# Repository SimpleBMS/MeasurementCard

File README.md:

This is a cool measurement card for SimpleBMS!

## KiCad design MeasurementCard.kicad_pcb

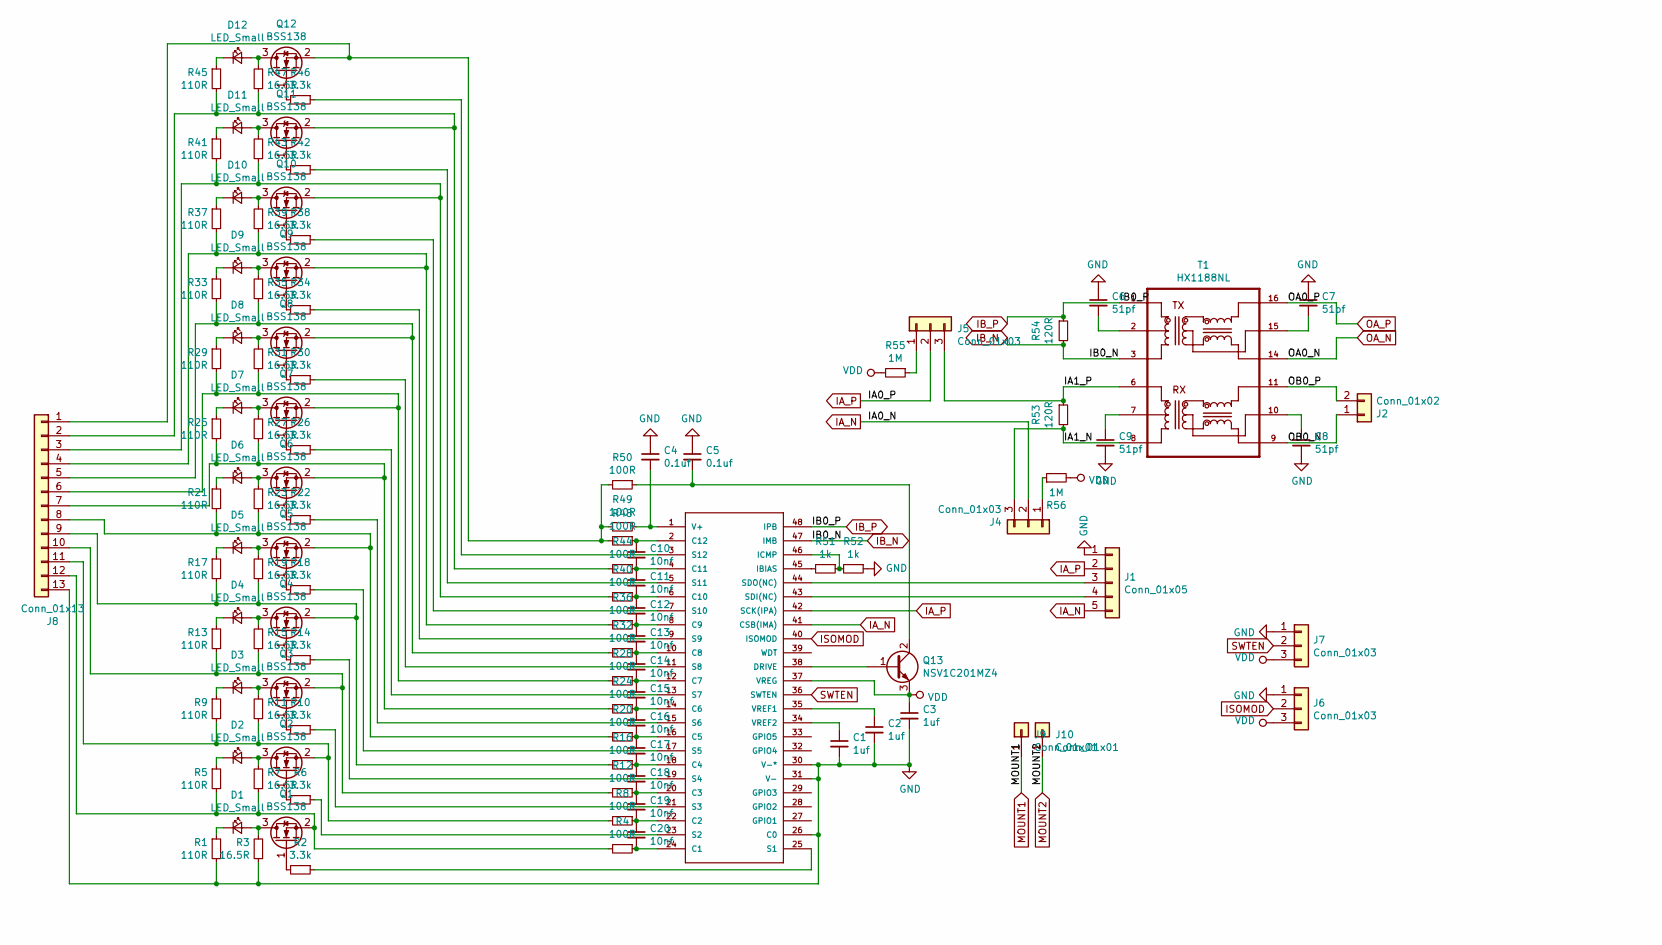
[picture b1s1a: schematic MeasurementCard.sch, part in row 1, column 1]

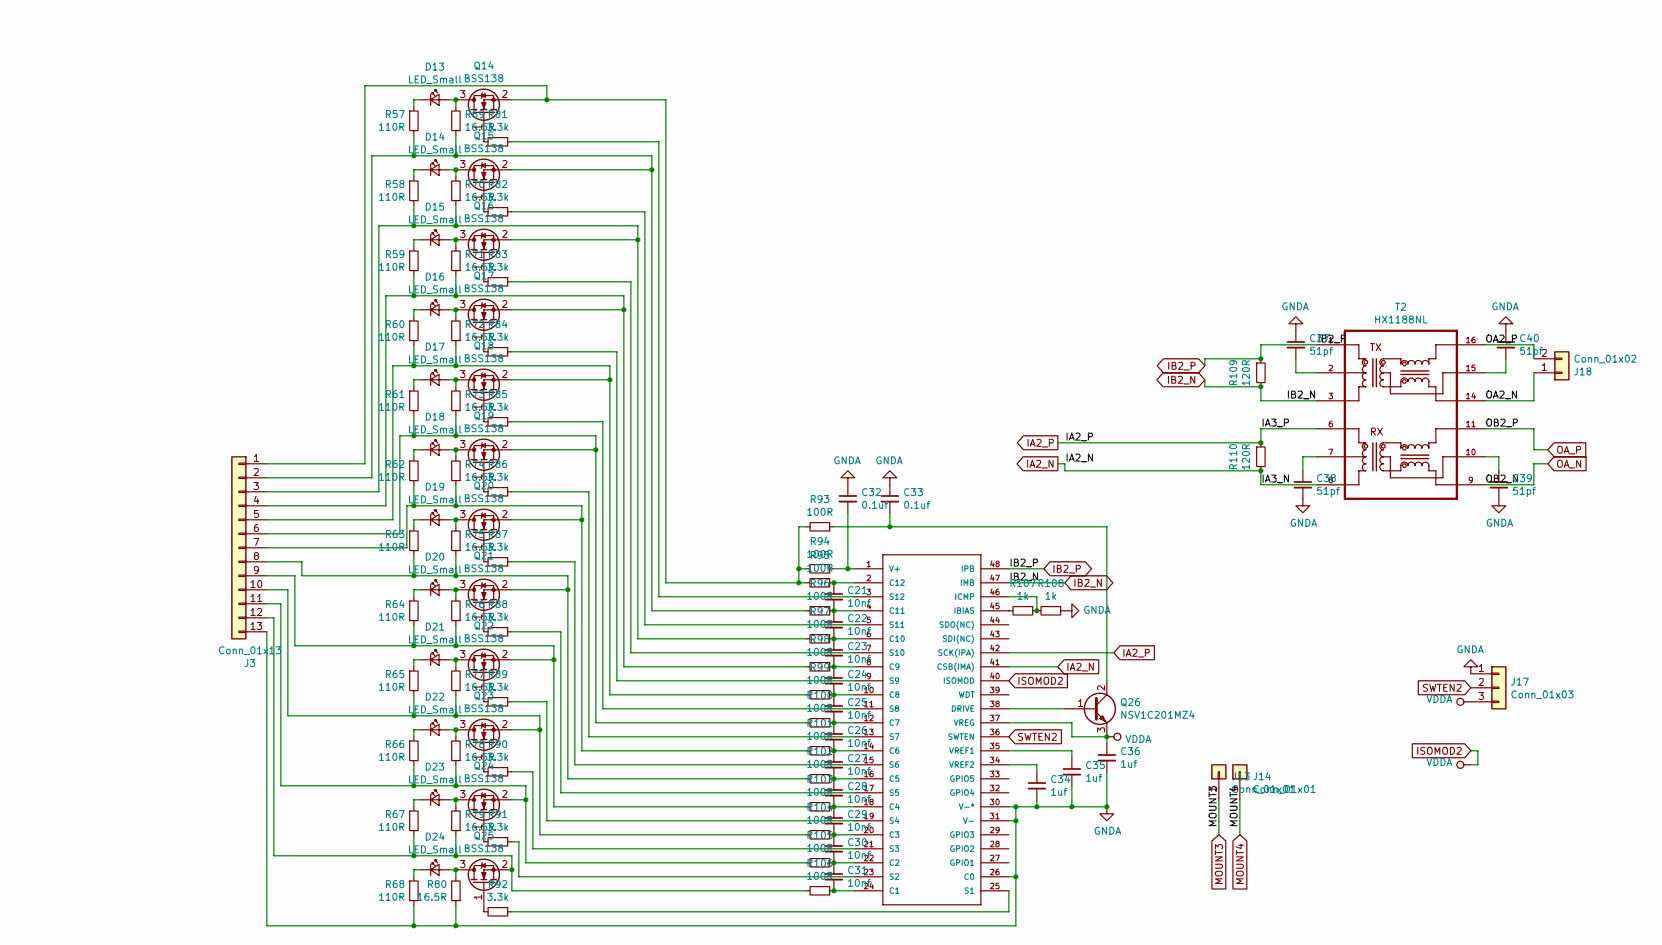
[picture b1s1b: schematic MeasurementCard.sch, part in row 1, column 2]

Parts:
C1, C2, C3, C34, C35, C36: 1uf; C_0805_2012Metric_Pad1.15x1.40mm_HandSolder
C4, C5, C32, C33: 0.1uf; C_0805_2012Metric_Pad1.15x1.40mm_HandSolder
C6, C7, C8, C9, C37, C38, C39, C40: 51pf; C_0805_2012Metric_Pad1.15x1.40mm_HandSolder
C10, C11, C12, C13, C14, C15, C16, C17, C18, C19, C20, C21, C22, C23, C24, C25, C26, C27, C28, C29, C30, C31: 10nf; C_0805_2012Metric_Pad1.15x1.40mm_HandSolder
D1, D2, D3, D4, D5, D6, D7, D8, D9, D10, D11, D12, D13, D14, D15, D16, D17, D18, D19, D20, D21, D22, D23, D24: LED_Small; LED_0603_1608Metric_Pad1.05x0.95mm_HandSolder
J1: Conn_01x05; JST_XH_S05B-XH-A_1x05_P2.50mm_Horizontal
J2, J18: Conn_01x02; JST_XH_S02B-XH-A_1x02_P2.50mm_Horizontal
J3, J8: Conn_01x13; JST_XH_S13B-XH-A_1x13_P2.50mm_Horizontal
J4, J5, J6, J7, J17: Conn_01x03; PinHeader_1x03_P2.54mm_Vertical
J9, J10, J13, J14: Conn_01x01; 1pin
Q1, Q2, Q3, Q4, Q5, Q6, Q7, Q8, Q9, Q10, Q11, Q12, Q14, Q15, Q16, Q17, Q18, Q19, Q20, Q21, Q22, Q23, Q24, Q25: BSS138; SOT-23
Q13, Q26: NSV1C201MZ4; SOT-223
R1, R5, R9, R13, R17, R21, R25, R29, R33, R37, R41, R45, R57, R58, R59, R60, R61, R62, R63, R64, R65, R66, R67, R68: 110R; R_0805_2012Metric_Pad1.15x1.40mm_HandSolder
R2, R6, R10, R14, R18, R22, R26, R30, R34, R38, R42, R46, R81, R82, R83, R84, R85, R86, R87, R88, R89, R90, R91, R92: 3.3k; R_0805_2012Metric_Pad1.15x1.40mm_HandSolder
R3, R7, R11, R15, R19, R23, R27, R31, R35, R39, R43, R47, R69, R70, R71, R72, R73, R74, R75, R76, R77, R78, R79, R80: 16.5R; R_2512_6332Metric_Pad1.52x3.35mm_HandSolder
R4, R8, R12, R16, R20, R24, R28, R32, R36, R40, R44, R48, R49, R50, R93, R94, R95, R96, R97, R98, R99, R100, R101, R102, R103, R104, R105, R106: 100R; R_0805_2012Metric_Pad1.15x1.40mm_HandSolder
R51, R52, R107, R108: 1k; R_0805_2012Metric_Pad1.15x1.40mm_HandSolder
R53, R54, R109, R110: 120R; R_0805_2012Metric_Pad1.15x1.40mm_HandSolder
R55, R56: 1M; R_0805_2012Metric_Pad1.15x1.40mm_HandSolder
T1, T2: HX1188NL; HXXXX
U1, U2: LTC6804-1; SOP50P780X200-48N

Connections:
/IA1_N: J4.3, R53.2, T1.8
/IA1_P: J5.3, R53.1, T1.6
/OA2_N: J18.1, T2.14
/OA2_P: J18.2, T2.16
/OB0_N: J2.1, T1.9
/OB0_P: J2.2, T1.11
GND: C1.2, C2.2, C3.2, C4.1, C5.1, C6.1, C7.1, C8.2, C9.2, J1.1, J6.1, J7.1, J8.13, R1.2, R3.1, R52.1, U1.26 (C0), U1.30 (V-*), U1.31 (V-)
GNDA: C32.1, C33.1, C34.2, C35.2, C36.2, C37.1, C38.2, C39.2, C40.1, J3.13, J17.1, R68.2, R80.1, R108.1, U2.26 (C0), U2.30 (V-*), U2.31 (V-)
IA2_N: R110.2, T2.8, U2.41 (CSB(IMA))
IA2_P: R110.1, T2.6, U2.42 (SCK(IPA))
IA_N: J1.5, J4.2, U1.41 (CSB(IMA))
IA_P: J1.2, J5.2, U1.42 (SCK(IPA))
IB2_N: R109.2, T2.3, U2.47 (IMB)
IB2_P: R109.1, T2.1, U2.48 (IPB)
IB_N: R54.2, T1.3, U1.47 (IMB)
IB_P: R54.1, T1.1, U1.48 (IPB)
ISOMOD: J6.2, U1.40 (ISOMOD)
ISOMOD2: C36.1, J17.3, Q26.3 (E), U2.37 (VREG), U2.40 (ISOMOD)
MOUNT1: J9.1
MOUNT2: J10.1
MOUNT3: J13.1
MOUNT4: J14.1
unnamed: C1.1, U1.34 (VREF2)
unnamed: C2.1, U1.35 (VREF1)
unnamed: C4.2, R49.1, U1.1 (V+)
unnamed: C5.2, Q13.2 (C), R50.1
unnamed: C6.2, T1.2
unnamed: C7.2, T1.15
unnamed: C8.1, T1.10
unnamed: C9.1, T1.7
unnamed: C10.1, R48.1, U1.2 (C12)
unnamed: C10.2, C11.1, R44.1, U1.4 (C11)
unnamed: C11.2, C12.1, R40.1, U1.6 (C10)
unnamed: C12.2, C13.1, R36.1, U1.8 (C9)
unnamed: C13.2, C14.1, R32.1, U1.10 (C8)
unnamed: C14.2, C15.1, R28.1, U1.12 (C7)
unnamed: C15.2, C16.1, R24.1, U1.14 (C6)
unnamed: C16.2, C17.1, R20.1, U1.16 (C5)
unnamed: C17.2, C18.1, R16.1, U1.18 (C4)
unnamed: C18.2, C19.1, R12.1, U1.20 (C3)
unnamed: C19.2, C20.1, R8.1, U1.22 (C2)
unnamed: C20.2, R4.1, U1.24 (C1)
unnamed: C21.1, R95.1, U2.2 (C12)
unnamed: C21.2, C22.1, R96.1, U2.4 (C11)
unnamed: C22.2, C23.1, R97.1, U2.6 (C10)
unnamed: C23.2, C24.1, R98.1, U2.8 (C9)
unnamed: C24.2, C25.1, R99.1, U2.10 (C8)
unnamed: C25.2, C26.1, R100.1, U2.12 (C7)
unnamed: C26.2, C27.1, R101.1, U2.14 (C6)
unnamed: C27.2, C28.1, R102.1, U2.16 (C5)
unnamed: C28.2, C29.1, R103.1, U2.18 (C4)
unnamed: C29.2, C30.1, R104.1, U2.20 (C3)
unnamed: C30.2, C31.1, R105.1, U2.22 (C2)
unnamed: C31.2, R106.1, U2.24 (C1)
unnamed: C32.2, R94.1, U2.1 (V+)
unnamed: C33.2, Q26.2 (C), R93.1
unnamed: C34.1, U2.34 (VREF2)
unnamed: C35.1, U2.35 (VREF1)
unnamed: C37.2, T2.2
unnamed: C38.1, T2.7
unnamed: C39.1, T2.10
unnamed: C40.2, T2.15
unnamed: D1.1 (K), R1.1
unnamed: D1.2 (A), Q1.3 (D), R3.2
unnamed: D2.1 (K), R5.1
unnamed: D2.2 (A), Q2.3 (D), R7.2
unnamed: D3.1 (K), R9.1
unnamed: D3.2 (A), Q3.3 (D), R11.2
unnamed: D4.1 (K), R13.1
unnamed: D4.2 (A), Q4.3 (D), R15.2
unnamed: D5.1 (K), R17.1
unnamed: D5.2 (A), Q5.3 (D), R19.2
unnamed: D6.1 (K), R21.1
unnamed: D6.2 (A), Q6.3 (D), R23.2
unnamed: D7.1 (K), R25.1
unnamed: D7.2 (A), Q7.3 (D), R27.2
unnamed: D8.1 (K), R29.1
unnamed: D8.2 (A), Q8.3 (D), R31.2
unnamed: D9.1 (K), R33.1
unnamed: D9.2 (A), Q9.3 (D), R35.2
unnamed: D10.1 (K), R37.1
unnamed: D10.2 (A), Q10.3 (D), R39.2
unnamed: D11.1 (K), R41.1
unnamed: D11.2 (A), Q11.3 (D), R43.2
unnamed: D12.1 (K), R45.1
unnamed: D12.2 (A), Q12.3 (D), R47.2
unnamed: D13.1 (K), R57.1
unnamed: D13.2 (A), Q14.3 (D), R69.2
unnamed: D14.1 (K), R58.1
unnamed: D14.2 (A), Q15.3 (D), R70.2
unnamed: D15.1 (K), R59.1
unnamed: D15.2 (A), Q16.3 (D), R71.2
unnamed: D16.1 (K), R60.1
unnamed: D16.2 (A), Q17.3 (D), R72.2
unnamed: D17.1 (K), R61.1
unnamed: D17.2 (A), Q18.3 (D), R73.2
unnamed: D18.1 (K), R62.1
unnamed: D18.2 (A), Q19.3 (D), R74.2
unnamed: D19.1 (K), R63.1
unnamed: D19.2 (A), Q20.3 (D), R75.2
unnamed: D20.1 (K), R64.1
unnamed: D20.2 (A), Q21.3 (D), R76.2
unnamed: D21.1 (K), R65.1
unnamed: D21.2 (A), Q22.3 (D), R77.2
unnamed: D22.1 (K), R66.1
unnamed: D22.2 (A), Q23.3 (D), R78.2
unnamed: D23.1 (K), R67.1
unnamed: D23.2 (A), Q24.3 (D), R79.2
unnamed: D24.1 (K), R68.1
unnamed: D24.2 (A), Q25.3 (D), R80.2
unnamed: J1.3, U1.44 (SDO(NC))
unnamed: J1.4, U1.43 (SDI(NC))
unnamed: J3.1, Q14.2 (S), R93.2, R94.2, R95.2
unnamed: J3.2, Q15.2 (S), R57.2, R69.1, R96.2
unnamed: J3.3, Q16.2 (S), R58.2, R70.1, R97.2
unnamed: J3.4, Q17.2 (S), R59.2, R71.1, R98.2
unnamed: J3.5, Q18.2 (S), R60.2, R72.1, R99.2
unnamed: J3.6, Q19.2 (S), R61.2, R73.1, R100.2
unnamed: J3.7, Q20.2 (S), R62.2, R74.1, R101.2
unnamed: J3.8, Q21.2 (S), R63.2, R75.1, R102.2
unnamed: J3.9, Q22.2 (S), R64.2, R76.1, R103.2
unnamed: J3.10, Q23.2 (S), R65.2, R77.1, R104.2
unnamed: J3.11, Q24.2 (S), R66.2, R78.1, R105.2
unnamed: J3.12, Q25.2 (S), R67.2, R79.1, R106.2
unnamed: J4.1, R56.1
unnamed: J5.1, R55.1
unnamed: J8.1, Q12.2 (S), R48.2, R49.2, R50.2
unnamed: J8.2, Q11.2 (S), R44.2, R45.2, R47.1
unnamed: J8.3, Q10.2 (S), R40.2, R41.2, R43.1
unnamed: J8.4, Q9.2 (S), R36.2, R37.2, R39.1
unnamed: J8.5, Q8.2 (S), R32.2, R33.2, R35.1
unnamed: J8.6, Q7.2 (S), R28.2, R29.2, R31.1
unnamed: J8.7, Q6.2 (S), R24.2, R25.2, R27.1
unnamed: J8.8, Q5.2 (S), R20.2, R21.2, R23.1
unnamed: J8.9, Q4.2 (S), R16.2, R17.2, R19.1
unnamed: J8.10, Q3.2 (S), R12.2, R13.2, R15.1
unnamed: J8.11, Q2.2 (S), R8.2, R9.2, R11.1
unnamed: J8.12, Q1.2 (S), R4.2, R5.2, R7.1
unnamed: Q1.1 (G), R2.2
unnamed: Q2.1 (G), R6.2
unnamed: Q3.1 (G), R10.2
unnamed: Q4.1 (G), R14.2
unnamed: Q5.1 (G), R18.2
unnamed: Q6.1 (G), R22.2
unnamed: Q7.1 (G), R26.2
unnamed: Q8.1 (G), R30.2
unnamed: Q9.1 (G), R34.2
unnamed: Q10.1 (G), R38.2
unnamed: Q11.1 (G), R42.2
unnamed: Q12.1 (G), R46.2
unnamed: Q13.1 (B), U1.38 (DRIVE)
unnamed: Q14.1 (G), R81.2
unnamed: Q15.1 (G), R82.2
unnamed: Q16.1 (G), R83.2
unnamed: Q17.1 (G), R84.2
unnamed: Q18.1 (G), R85.2
unnamed: Q19.1 (G), R86.2
unnamed: Q20.1 (G), R87.2
unnamed: Q21.1 (G), R88.2
unnamed: Q22.1 (G), R89.2
unnamed: Q23.1 (G), R90.2
unnamed: Q24.1 (G), R91.2
unnamed: Q25.1 (G), R92.2
unnamed: Q26.1 (B), U2.38 (DRIVE)
unnamed: R2.1, U1.25 (S1)
unnamed: R6.1, U1.23 (S2)
unnamed: R10.1, U1.21 (S3)
unnamed: R14.1, U1.19 (S4)
unnamed: R18.1, U1.17 (S5)
unnamed: R22.1, U1.15 (S6)
unnamed: R26.1, U1.13 (S7)
unnamed: R30.1, U1.11 (S8)
unnamed: R34.1, U1.9 (S9)
unnamed: R38.1, U1.7 (S10)
unnamed: R42.1, U1.5 (S11)
unnamed: R46.1, U1.3 (S12)
unnamed: R51.1, R52.2, U1.46 (ICMP)
unnamed: R51.2, U1.45 (IBIAS)
unnamed: R81.1, U2.3 (S12)
unnamed: R82.1, U2.5 (S11)
unnamed: R83.1, U2.7 (S10)
unnamed: R84.1, U2.9 (S9)
unnamed: R85.1, U2.11 (S8)
unnamed: R86.1, U2.13 (S7)
unnamed: R87.1, U2.15 (S6)
unnamed: R88.1, U2.17 (S5)
unnamed: R89.1, U2.19 (S4)
unnamed: R90.1, U2.21 (S3)
unnamed: R91.1, U2.23 (S2)
unnamed: R92.1, U2.25 (S1)
unnamed: R107.1, R108.2, U2.46 (ICMP)
unnamed: R107.2, U2.45 (IBIAS)
OA_N: T1.14, T2.9
OA_P: T1.16, T2.11
SWTEN: J7.2, U1.36 (SWTEN)
SWTEN2: J17.2, U2.36 (SWTEN)
VDD: C3.1, J6.3, J7.3, Q13.3 (E), R55.2, R56.2, U1.37 (VREG)

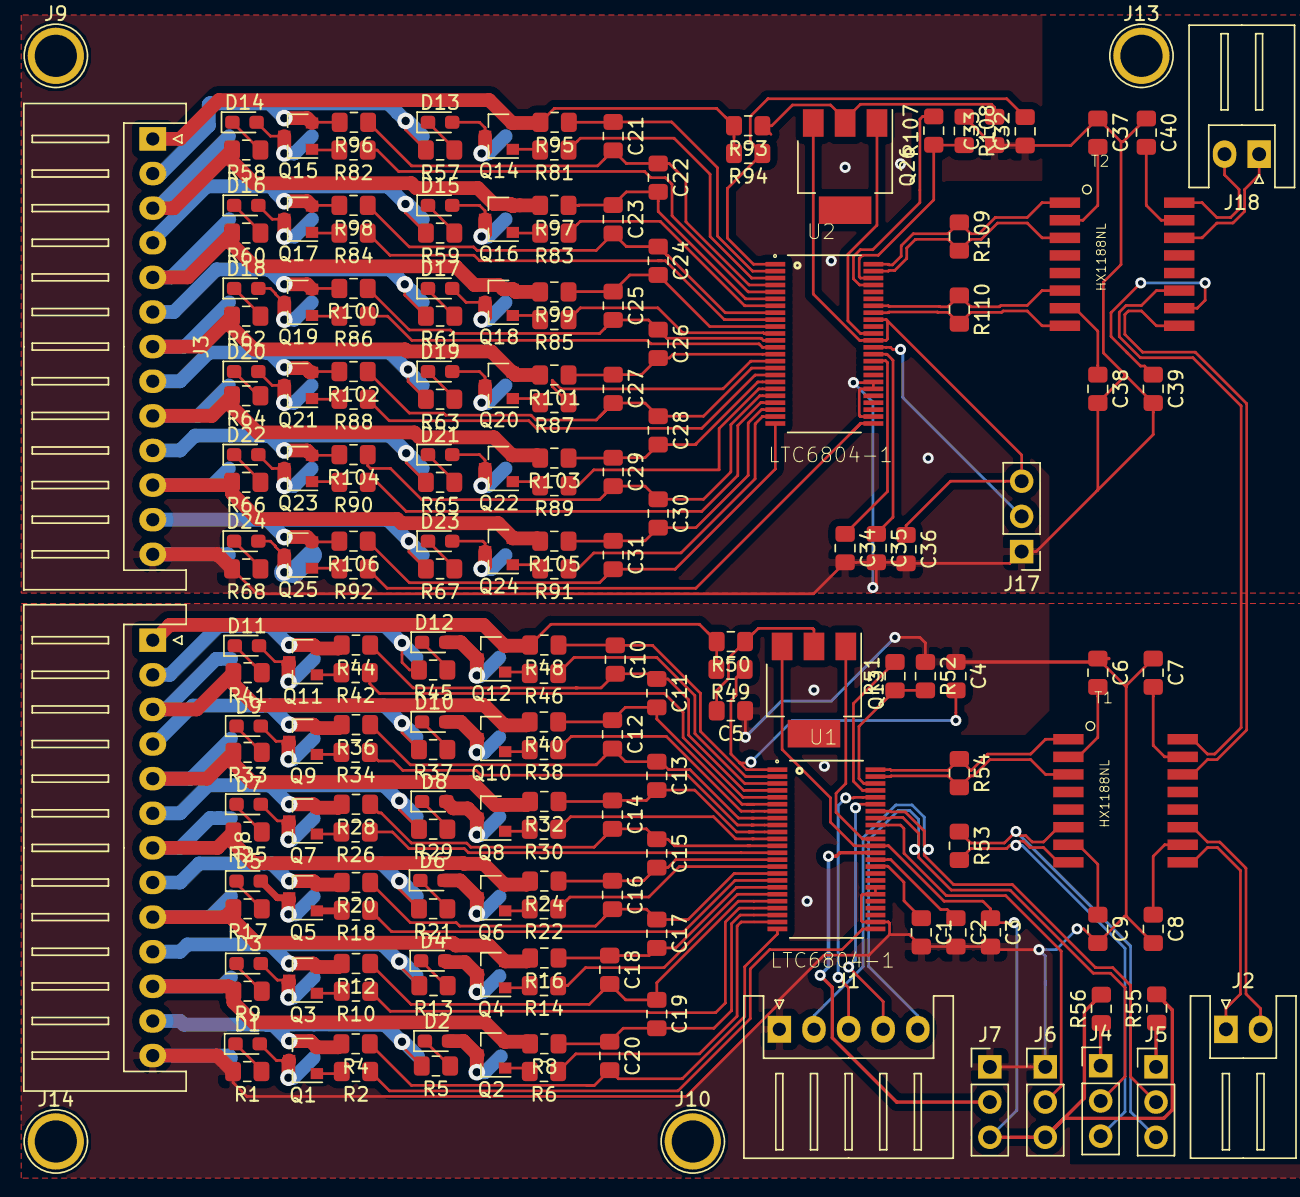
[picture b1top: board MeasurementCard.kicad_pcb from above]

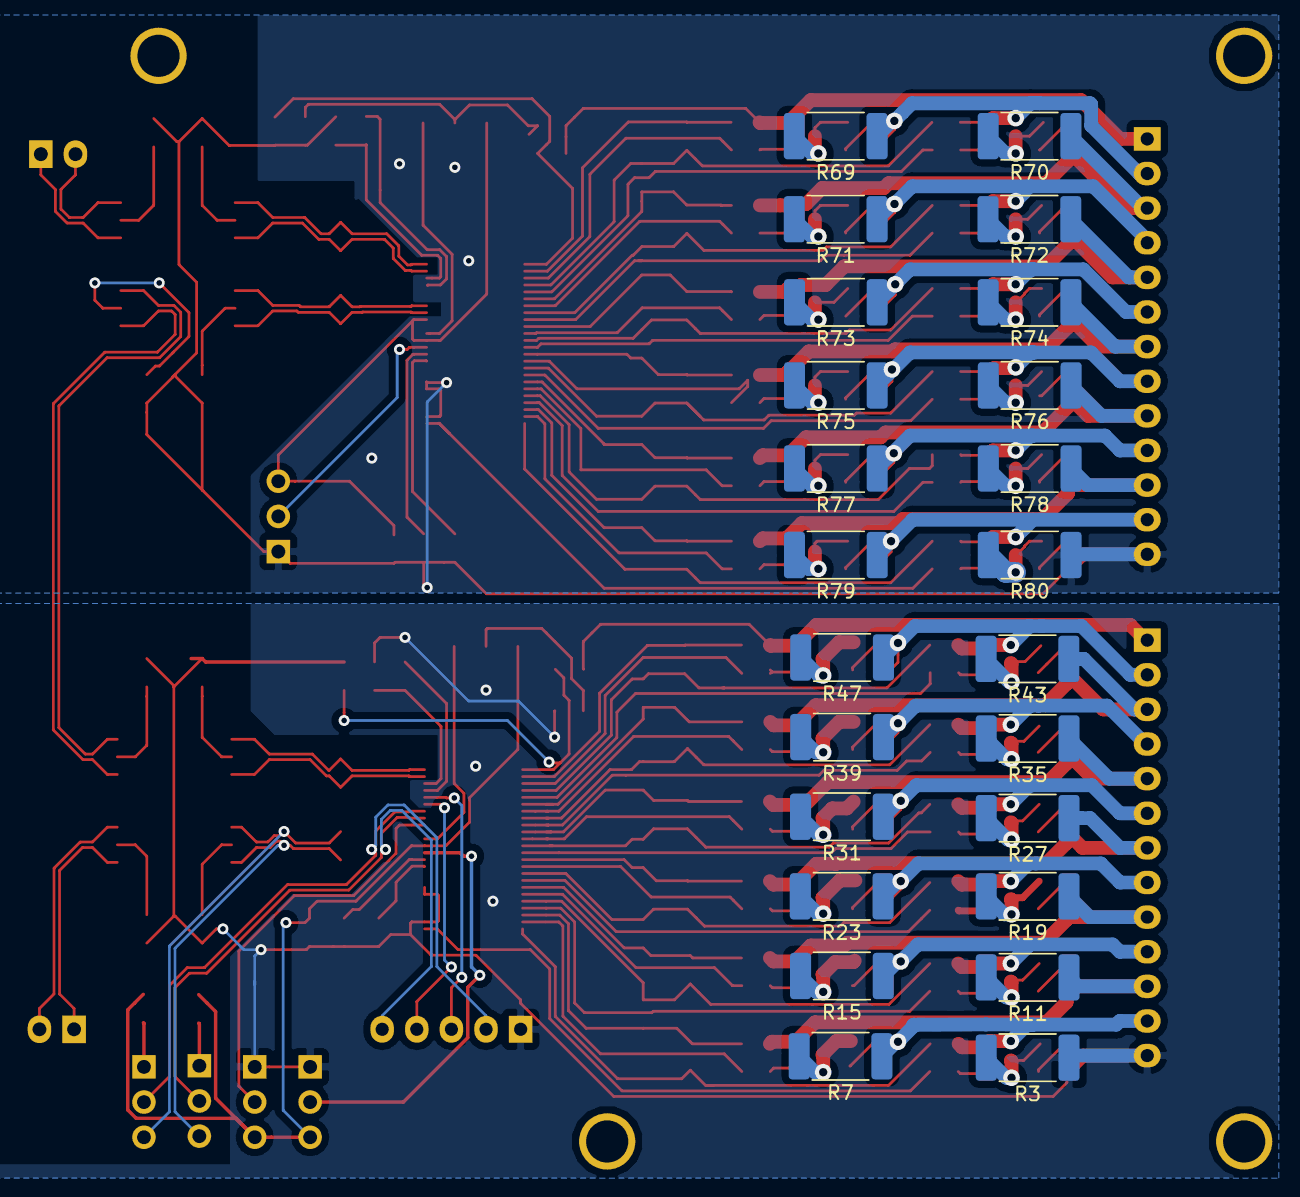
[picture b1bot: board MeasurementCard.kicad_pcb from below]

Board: 2 copper layers, 218 parts (24 on the bottom side), 193 nets.

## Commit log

2019-04-03 readme
2019-07-05 added db25 + thermistor support
